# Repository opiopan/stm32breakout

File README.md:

Breakout Board for STM32
===

This hardware design is published under open source lincence. You can use and modify this design freely. There is also no limitation in commercial use.

This breakout board is designed to install any QFP32 formfactor STM32 chip, and following functions are installed.

- +3.3V power supplay translated from micro USB +5V input
- 16MHz crystal to genarate accurate clock which enable to drive USB
- two buttons to reset and to specify boot mode
- 4 pin connector for debugger (SWCLK, SWDIO, NRST, and GND)
- USB data signal pins (PA11, PA12) are exported via micro USB connector, that means you can use DFU to download firmware

Please note that USB data communication function doesn't work if a STM32 MCU which has no USB functionality such as [STM32F303K8](https://www.st.com/content/st_com/en/products/microcontrollers-microprocessors/stm32-32-bit-arm-cortex-mcus/stm32-mainstream-mcus/stm32f3-series/stm32f303/stm32f303k8.html#design-scroll).<br>
[STM32F042K6](https://www.st.com/content/st_com/en/products/microcontrollers-microprocessors/stm32-32-bit-arm-cortex-mcus/stm32-mainstream-mcus/stm32f0-series/stm32f0x2/stm32f042k6.html) is a good candidate to use all function of this breakout board.

## PCB Design
Eagle PCB design files are placed at [here](./pcb/).

## BOM list

Components | Value / Product Number | Remarks
-----------|------------------------|------------------------------
U1         | STM32 (QFP32)          |
U2         | MCP1703AT-3302E/CB     | SOT-23A 3.3V LDO
J1         | ZX62-B-5PA(33)         | Hirose Micro USB female connector
X1         | 16MHz Crystal (3225)   | load capacitance: 10pF
C1, C2, C9 | 1uF (1005)             |
C3, C4, C10| 0.1uF (1005)           |
C5         | 4.7uF (1005)           |
C6, C7     | 15pF (1005)            | need to change value if X1's load capacitance is not 10pF
C8         | 10nF (1005)
R1         | 10k ohm (1005)         |

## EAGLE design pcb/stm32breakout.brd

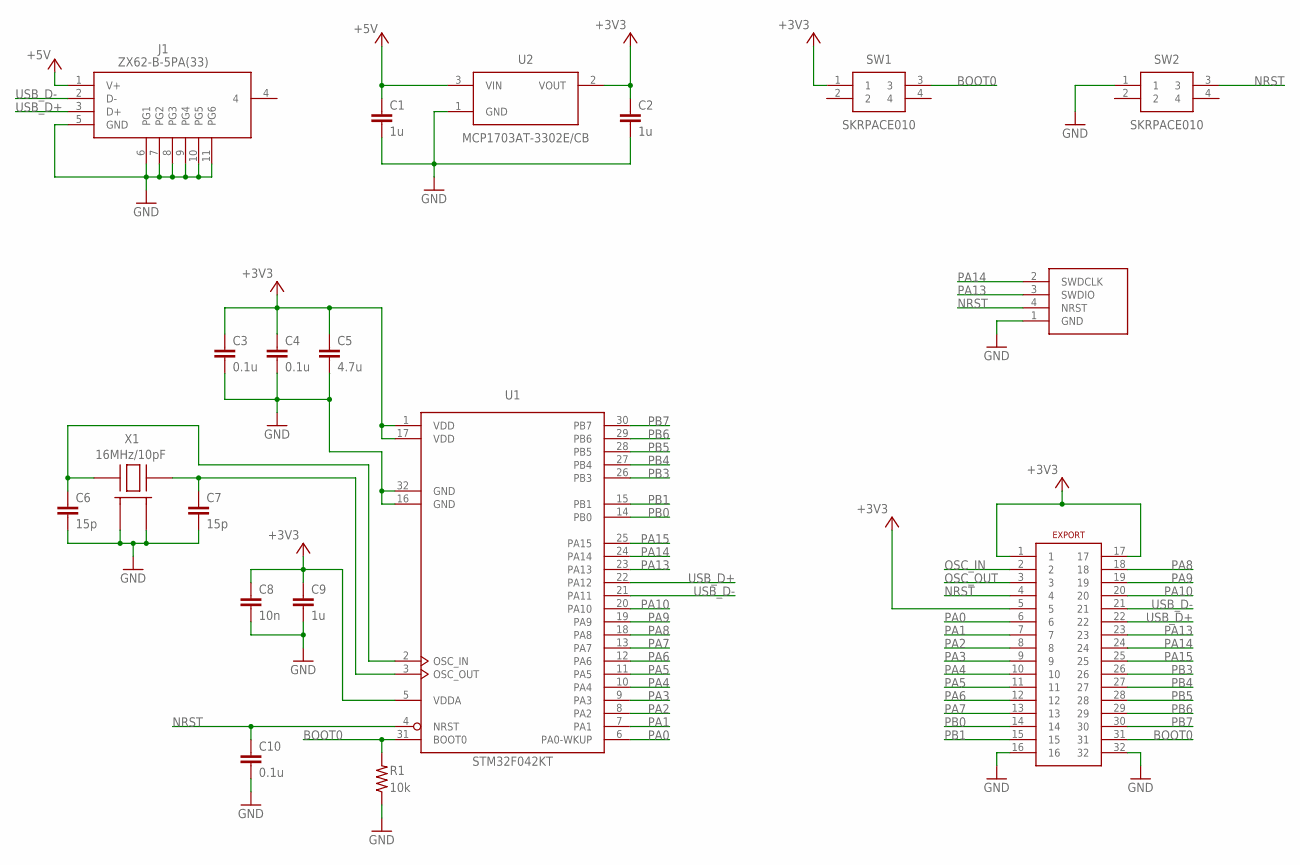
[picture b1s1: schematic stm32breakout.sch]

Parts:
C1, C2, C9: 1u; RCL_C0402_HS
C3, C4, C10: 0.1u; RCL_C0402_HS
C5: 4.7u; RCL_C0402_HS
C6, C7: 15p; RCL_C0402_HS
C8: 10n; RCL_C0402_HS
EXPORT: 2X16PIN
J1: ZX62-B-5PA(33); ZX62-B-5PA(33)-TRUE-HANDSOLD
R1: 10k; RCL_R0402_HS
SW1, SW2: SKRPACE010; SMT(4.2X3.2)
U1: STM32F042KT; LQFP32-M
U2: MCP1703AT-3302E/CB; SOT23
U$1: 4PIN-DEBUG
X1: 16MHz/10pF; CRYSTAL3225-HS

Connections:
+3V3: C2.1, C3.1, C4.1, C5.1, C8.1, C9.1, EXPORT.1, EXPORT.5, EXPORT.17, SW1.1, U1.1 (VDD), U1.5 (VDDA), U1.17 (VDD), U2.2 (VOUT)
+5V: C1.1, J1.1 (V+), U2.3 (VIN)
BOOT0: EXPORT.31, R1.2, SW1.3, U1.31 (BOOT0)
GND: C1.2, C2.2, C3.2, C4.2, C5.2, C6.2, C7.2, C8.2, C9.2, C10.2, EXPORT.16, EXPORT.32, J1.5 (GND), J1.6 (PG1), J1.7 (PG2), J1.8 (PG3), J1.9 (PG4), J1.10 (PG5), J1.11 (PG6), R1.1, SW2.1, U1.16 (GND), U1.32 (GND), U2.1 (GND), U$1.1 (GND), X1.2 (GND_1), X1.4 (GND_2)
NRST: C10.1, EXPORT.4, SW2.3, U1.4 (NRST), U$1.4 (NRST)
OSC_IN: C6.1, EXPORT.2, U1.2 (OSC_IN), X1.1 (HOT_1)
OSC_OUT: C7.1, EXPORT.3, U1.3 (OSC_OUT), X1.3 (HOT_2)
PA0: EXPORT.6, U1.6 (PA0-WKUP)
PA1: EXPORT.7, U1.7 (PA1)
PA2: EXPORT.8, U1.8 (PA2)
PA3: EXPORT.9, U1.9 (PA3)
PA4: EXPORT.10, U1.10 (PA4)
PA5: EXPORT.11, U1.11 (PA5)
PA6: EXPORT.12, U1.12 (PA6)
PA7: EXPORT.13, U1.13 (PA7)
PA8: EXPORT.18, U1.18 (PA8)
PA9: EXPORT.19, U1.19 (PA9)
PA10: EXPORT.20, U1.20 (PA10)
PA13: EXPORT.23, U1.23 (PA13), U$1.3 (SWDIO)
PA14: EXPORT.24, U1.24 (PA14), U$1.2 (SWDCLK)
PA15: EXPORT.25, U1.25 (PA15)
PB0: EXPORT.14, U1.14 (PB0)
PB1: EXPORT.15, U1.15 (PB1)
PB3: EXPORT.26, U1.26 (PB3)
PB4: EXPORT.27, U1.27 (PB4)
PB5: EXPORT.28, U1.28 (PB5)
PB6: EXPORT.29, U1.29 (PB6)
PB7: EXPORT.30, U1.30 (PB7)
USB_D+: EXPORT.22, J1.3 (D+), U1.22 (PA12)
USB_D-: EXPORT.21, J1.2 (D-), U1.21 (PA11)

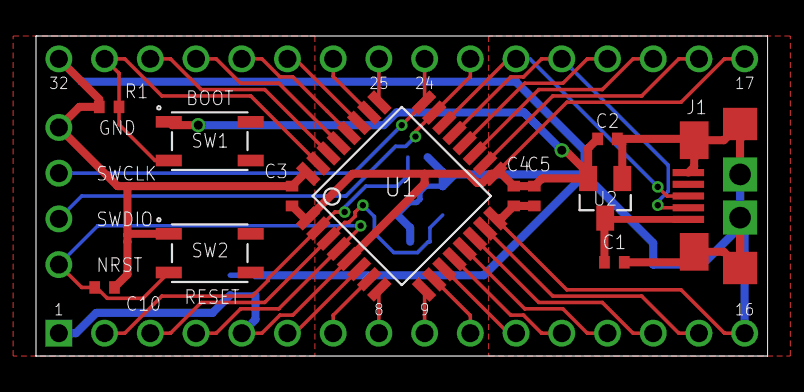
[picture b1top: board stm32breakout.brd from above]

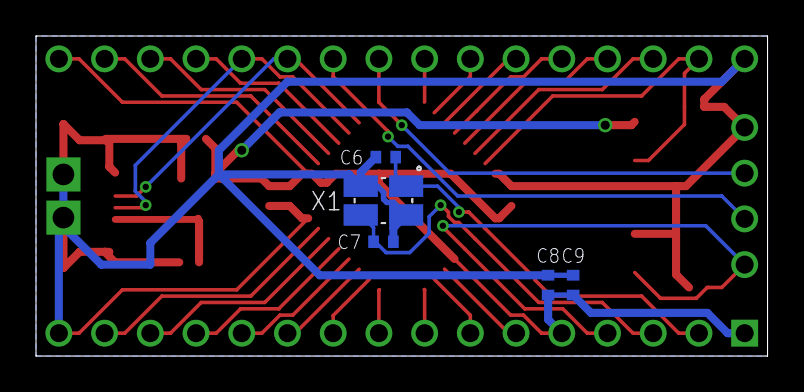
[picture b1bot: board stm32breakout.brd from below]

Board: 2 copper layers, 40.6 x 17.8 mm, 19 parts (5 on the bottom side), 30 nets.

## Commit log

2019-03-31 add panelizing script
